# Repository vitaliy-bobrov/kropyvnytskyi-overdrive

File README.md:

# Kropyvnytskyi Overdrive

Kropyvnytskyi Overdrive - modified Exar OD-02 OverDrive KiCad files.

The repository contains KiCad source files: schematic, PCB, BOM.

## Schematic

## PCB (3D preview)

## Interactive BOM

👉 [BOM](https://vitaliy-bobrov.github.io/kropyvnytskyi-overdrive/)

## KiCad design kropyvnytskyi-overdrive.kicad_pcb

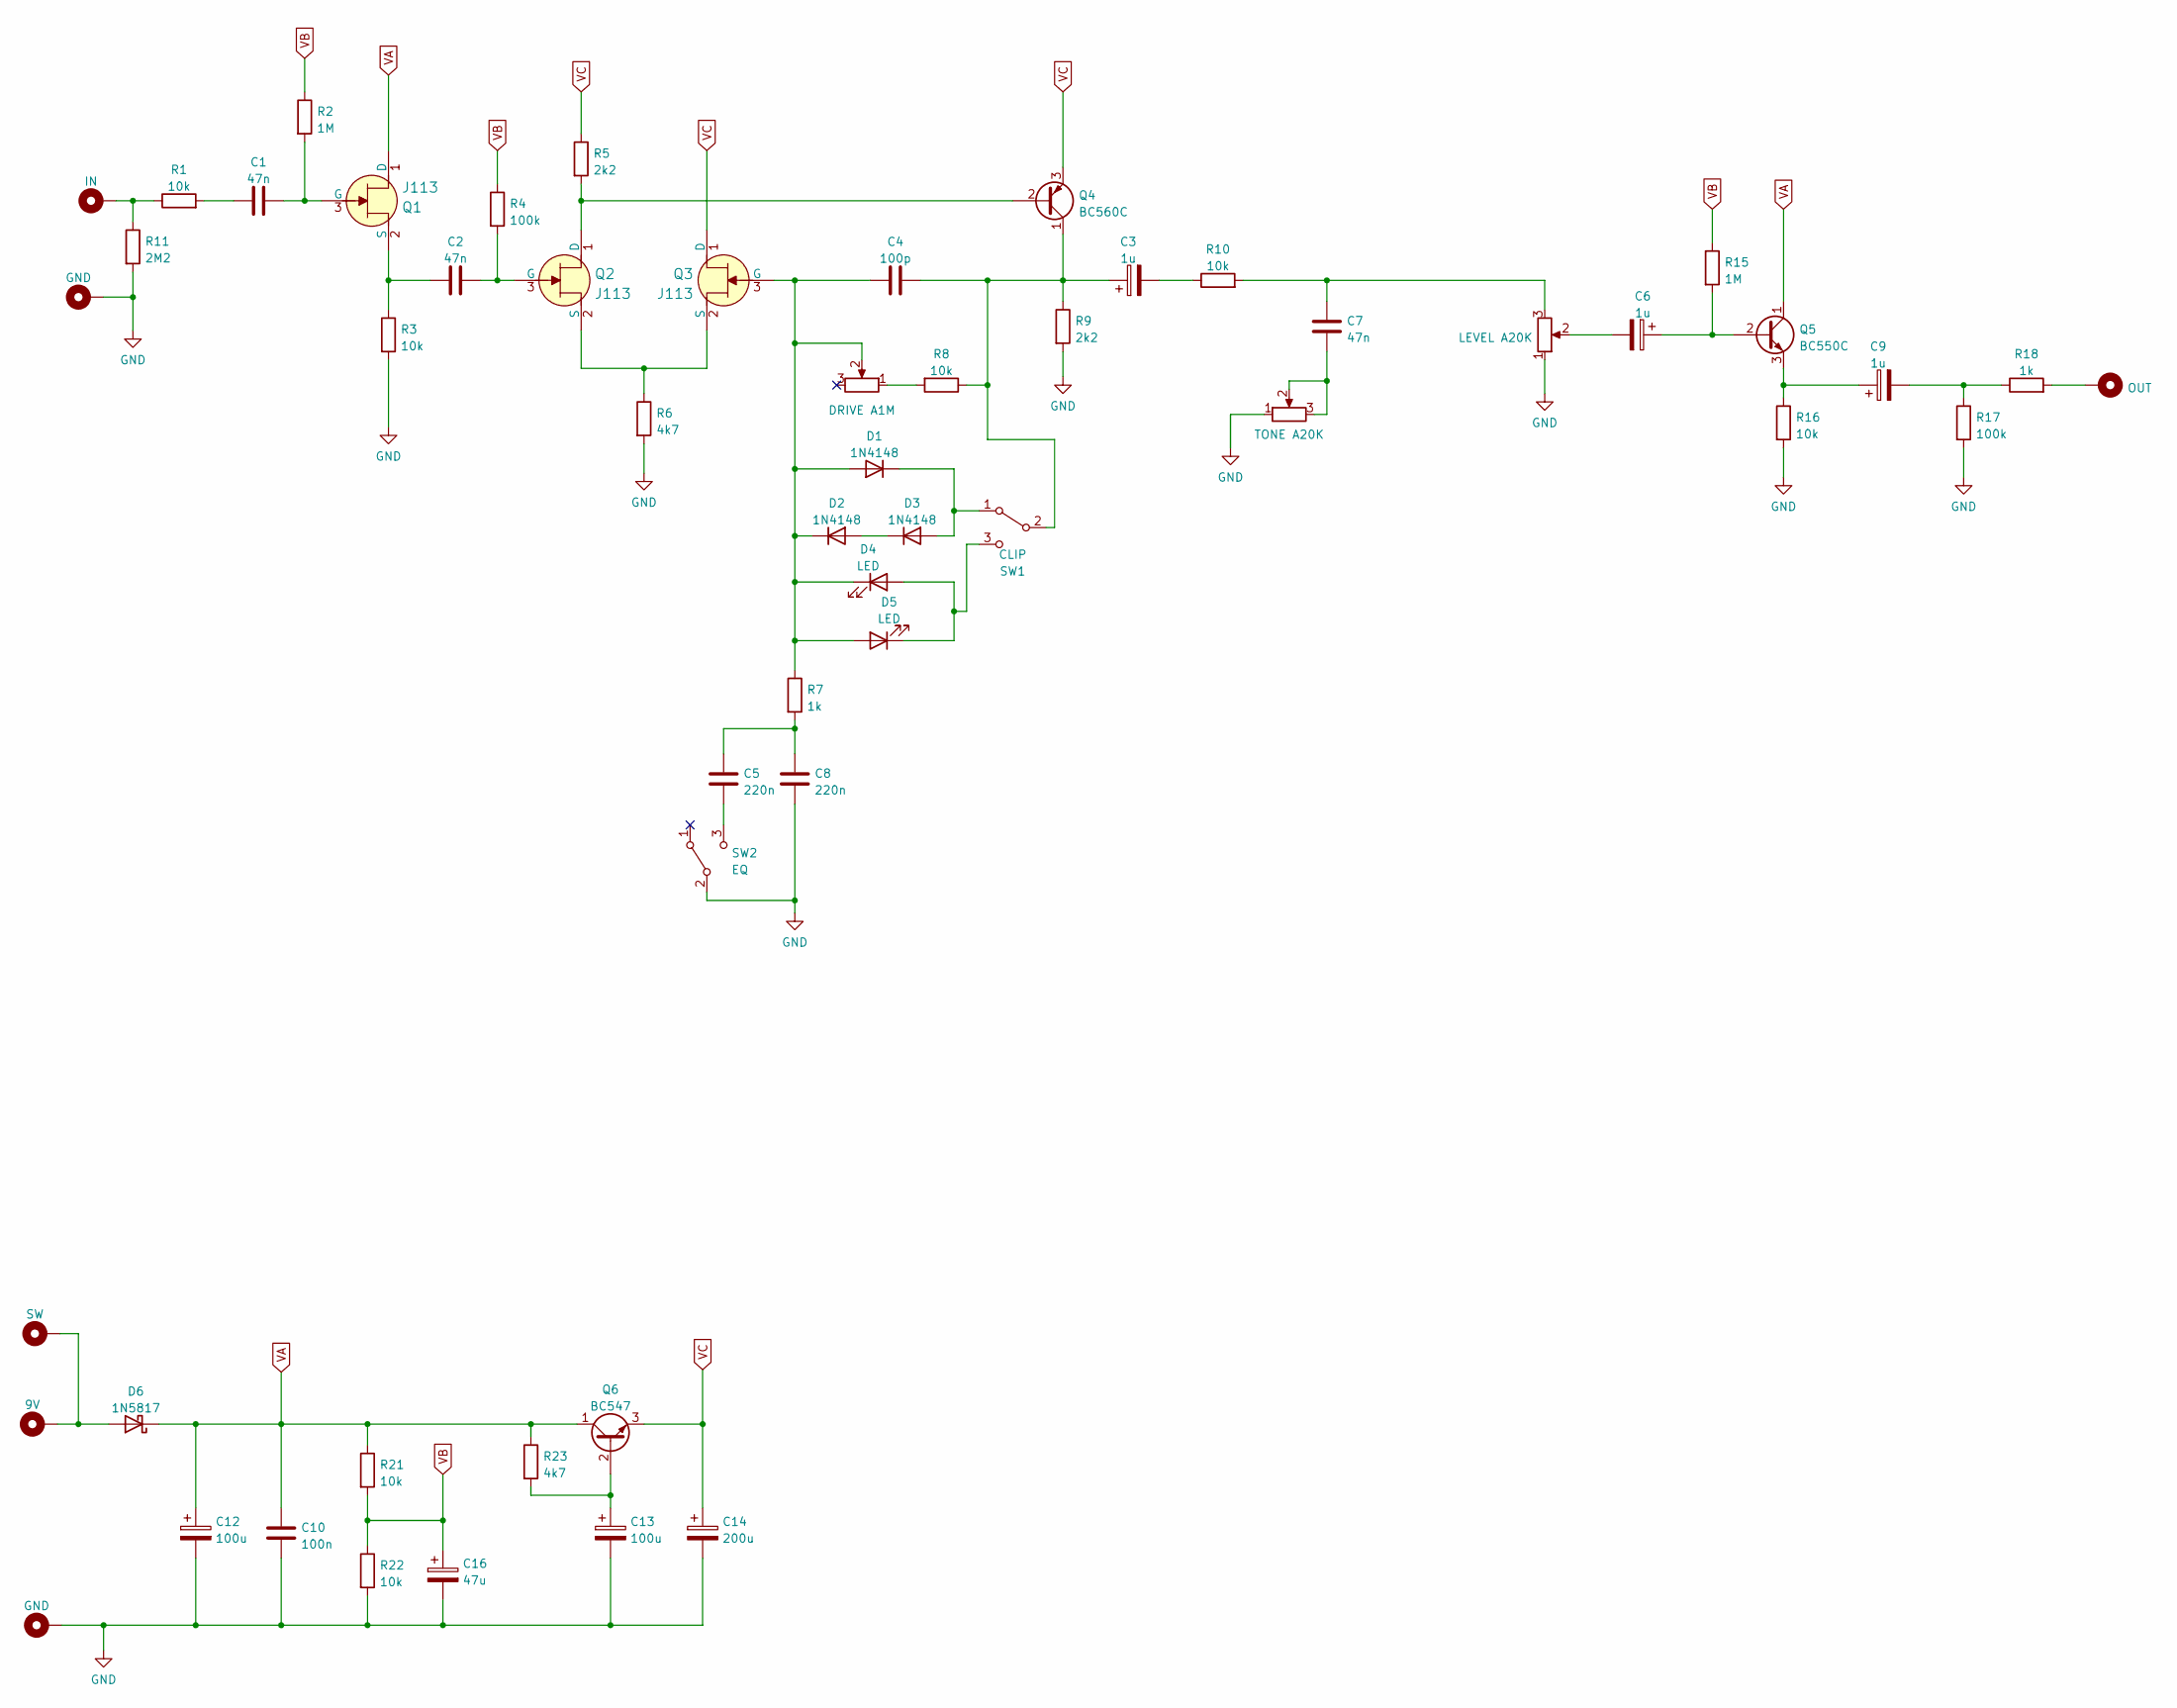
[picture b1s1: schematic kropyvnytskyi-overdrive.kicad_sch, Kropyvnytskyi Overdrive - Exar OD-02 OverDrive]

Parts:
C1, C2, C7: 47n; 0.2_22.SML
C3, C6, C9: 1u; 0502
C4: 100p; 0.2%22.MED
C5, C8: 220n; 0.2_22_7_5.SML
C10: 100n; 0.2_22.SML
C12, C13: 100u; 0632
C14: 200u; 0632
C16: 47u; 0502
D1, D2, D3: 1N4148; DO35-3
D4, D5: LED; 3MM_1
D6: 1N5817; DO41-3
H1: IN; PAD1
H2: SW; PAD1
H3: OUT; PAD1
H7, H10: GND; PAD3
H9: 9V; PAD1
Q1, Q2, Q3: J113; TO92; MPN J113; Digi-Key_PN J113FS-ND
Q4: BC560C; TO92
Q5: BC550C; TO92
Q6: BC547; TO92
R1, R3, R8, R10, R16, R21, R22: 10k; 0.2_22
R2, R15: 1M; 0.2_22
R4, R17: 100k; 0.2_22
R5, R9: 2k2; 0.2_22
R6, R23: 4k7; 0.2_22
R7, R18: 1k; 0.2_22
R11: 2M2; 0.2_22
RV1: LEVEL A20K; 16MM_B.MOUNT_BANZAI
RV2: DRIVE A1M; 16MM_B.MOUNT_BANZAI
RV3: TONE A20K; 16MM_B.MOUNT_BANZAI
SW1: CLIP; SPDT.LUGS
SW2: EQ; SPDT.LUGS

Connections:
GND: C8.2, C10.2, C12.2, C13.2, C14.2, C16.2, H7.1, H10.1, R3.2, R6.2, R9.2, R11.2, R16.2, R17.2, R22.2, RV1.1, RV3.1, SW2.2 (B)
unnamed: C1.1, R1.2
unnamed: C3.2, R10.1
unnamed: C5.1, C8.1, R7.2
unnamed: C6.2, RV1.2
unnamed: C7.1, R10.2, RV1.3
unnamed: C7.2, RV3.2, RV3.3
unnamed: C9.2, R17.1, R18.1
unnamed: C4.1, D1.2 (A), D2.1 (K), D4.1 (K), D5.2 (A), Q3.3 (G), R7.1, RV2.2
unnamed: D1.1 (K), D3.2 (A), SW1.1 (A)
unnamed: D2.2 (A), D3.1 (K)
unnamed: D4.2 (A), D5.1 (K), SW1.3 (C)
unnamed: D6.2 (A), H2.1, H9.1
unnamed: H1.1, R1.1, R11.1
unnamed: H3.1, R18.2
unnamed: C1.2, Q1.3 (G), R2.2
unnamed: C2.1, Q1.2 (S), R3.1
unnamed: Q2.1 (D), Q4.2 (B), R5.2
unnamed: C2.2, Q2.3 (G), R4.2
unnamed: Q2.2 (S), Q3.2 (S), R6.1
unnamed: C3.1, C4.2, Q4.1 (C), R8.1, R9.1, SW1.2 (B)
unnamed: C6.1, Q5.2 (B), R15.2
unnamed: C9.1, Q5.3 (E), R16.1
unnamed: C13.1, Q6.2 (B), R23.2
unnamed: R8.2, RV2.1
unnamed: C5.2, SW2.3 (C)
VA: C10.1, C12.1, D6.1 (K), Q1.1 (D), Q5.1 (C), Q6.1 (C), R21.1, R23.1
VB: C16.1, R2.1, R4.1, R15.1, R21.2, R22.1
VC: C14.1, Q3.1 (D), Q4.3 (E), Q6.3 (E), R5.1

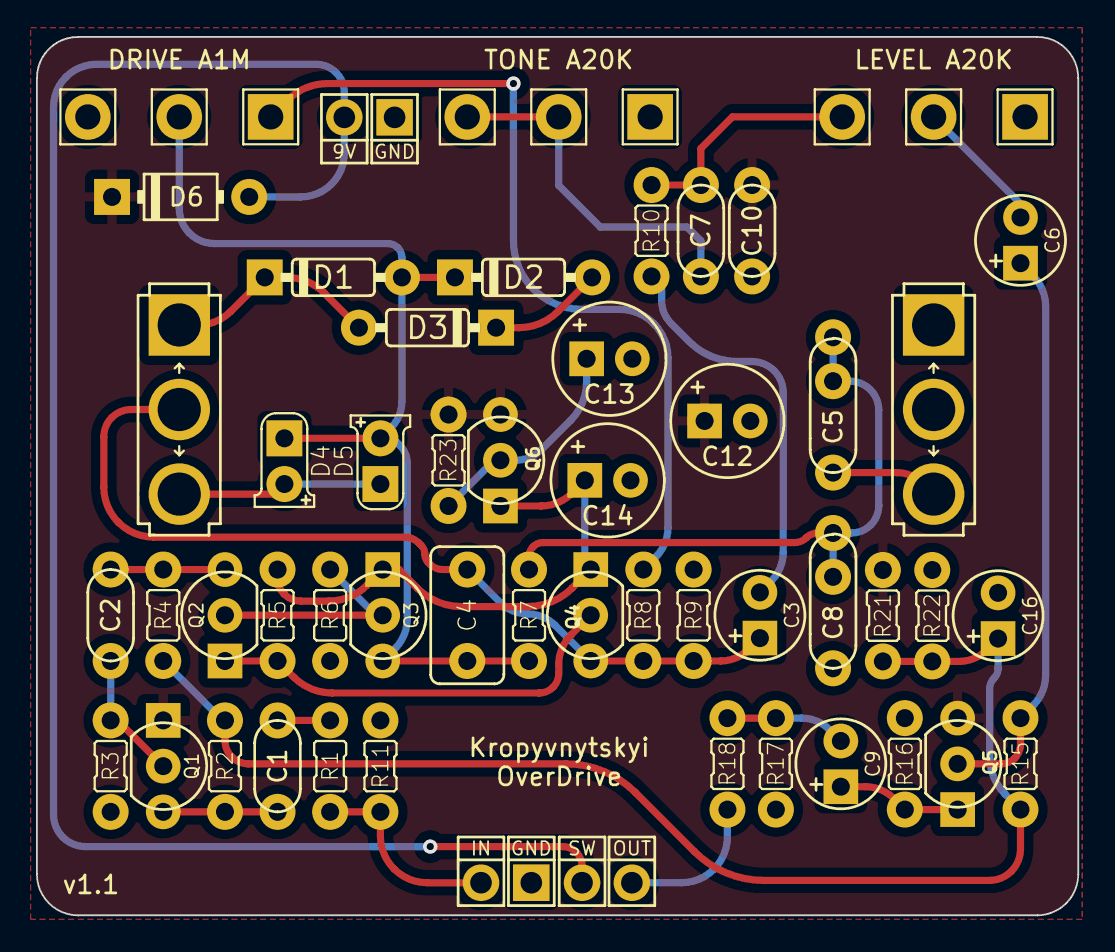
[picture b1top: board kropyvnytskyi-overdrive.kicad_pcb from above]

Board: 2 copper layers, 57.9 x 48.8 mm, 55 parts (0 on the bottom side), 29 nets.

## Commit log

2023-06-06 v1.0
2023-06-06 fix readme
